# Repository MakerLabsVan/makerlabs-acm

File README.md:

# makerlabs-acm
MakerLabs Access Control Management (ACM) System

## How-to obtain this repo:
# Clone this repo recursively:
```
git clone --recursive https://github.com/MakerLabsVan/makerlabs-acm
cd makerlabs-acm
```

# Pre-requisites (macOS):

- Electrical:
  Install KiCad 5.0+:
  http://downloads.kicad-pcb.org/osx/nightly/

- Firmware/Software:
  Install homebrew macOS package manager:
  ```
  /usr/bin/ruby -e "$(curl -fsSL https://raw.githubusercontent.com/Homebrew/install/master/install)"
  ```

  Install `yarn`:
  ```
  brew install yarn
  ```

  Install dependencies:
  ```
  yarn deps
  yarn install
  ```

# Electrical

- Open the KiCad project:
  ```
  open -a kicad electrical/makerlabs-acm-reader-lock_v1.0.0.pro
  ```

# Firmware

- Configure firmware settings (Wifi SSID/password, Google Spreadsheet ID, etc):
  ```
  yarn firmware menuconfig
  ```

- Build a firmware image, flash it to the connected board:
  ```
  yarn firmware flash
  ```

- Same as above, but also monitor the serial data and reboot after flashing:
  ```
  yarn firmware flash monitor
  ```

- Build binaries for OTA firmware updates, upload them to Google Drive:
  (*note: increment the number in the `firmware/VERSION` file to allow clients to download it*)
  ```
  yarn firmware all_binaries && \
    gdrive update <firmware_image_id> firmware/build/makerlabs-acm-reader-lock.bin && \
    gdrive update <firmware_update_id> firmware/build/latest.fw.fb
  ```

# WebComponents

- Add WebComponent dependencies in webcomponents, via `bower`:
  ```
  yarn webcomponents-add <component names>
  ```

- Fetch/update WebComponent versions from latest packages:
  ```
  yarn webcomponents
  ```

Commit and push the updated files in `webcomponents/` and `webcomponents/bower_components/`

# Google Apps Script Webapp / Frontend

- Login to the Google Apps Script / online UI:
  ```
  yarn login
  ```

  Enable the Google Apps Script API for your personal Google Apps user:
  https://script.google.com/home/usersettings

- Pull changes from Google Apps Script / online UI:
  ```
  yarn pull
  ```

- (Make desired changes to files in `webapp/`)

- Push changes to Google Apps Script
  ```
  yarn push
  ```

- Deploy the latest changes as a webapp:
  ```
  yarn deploy
  ```

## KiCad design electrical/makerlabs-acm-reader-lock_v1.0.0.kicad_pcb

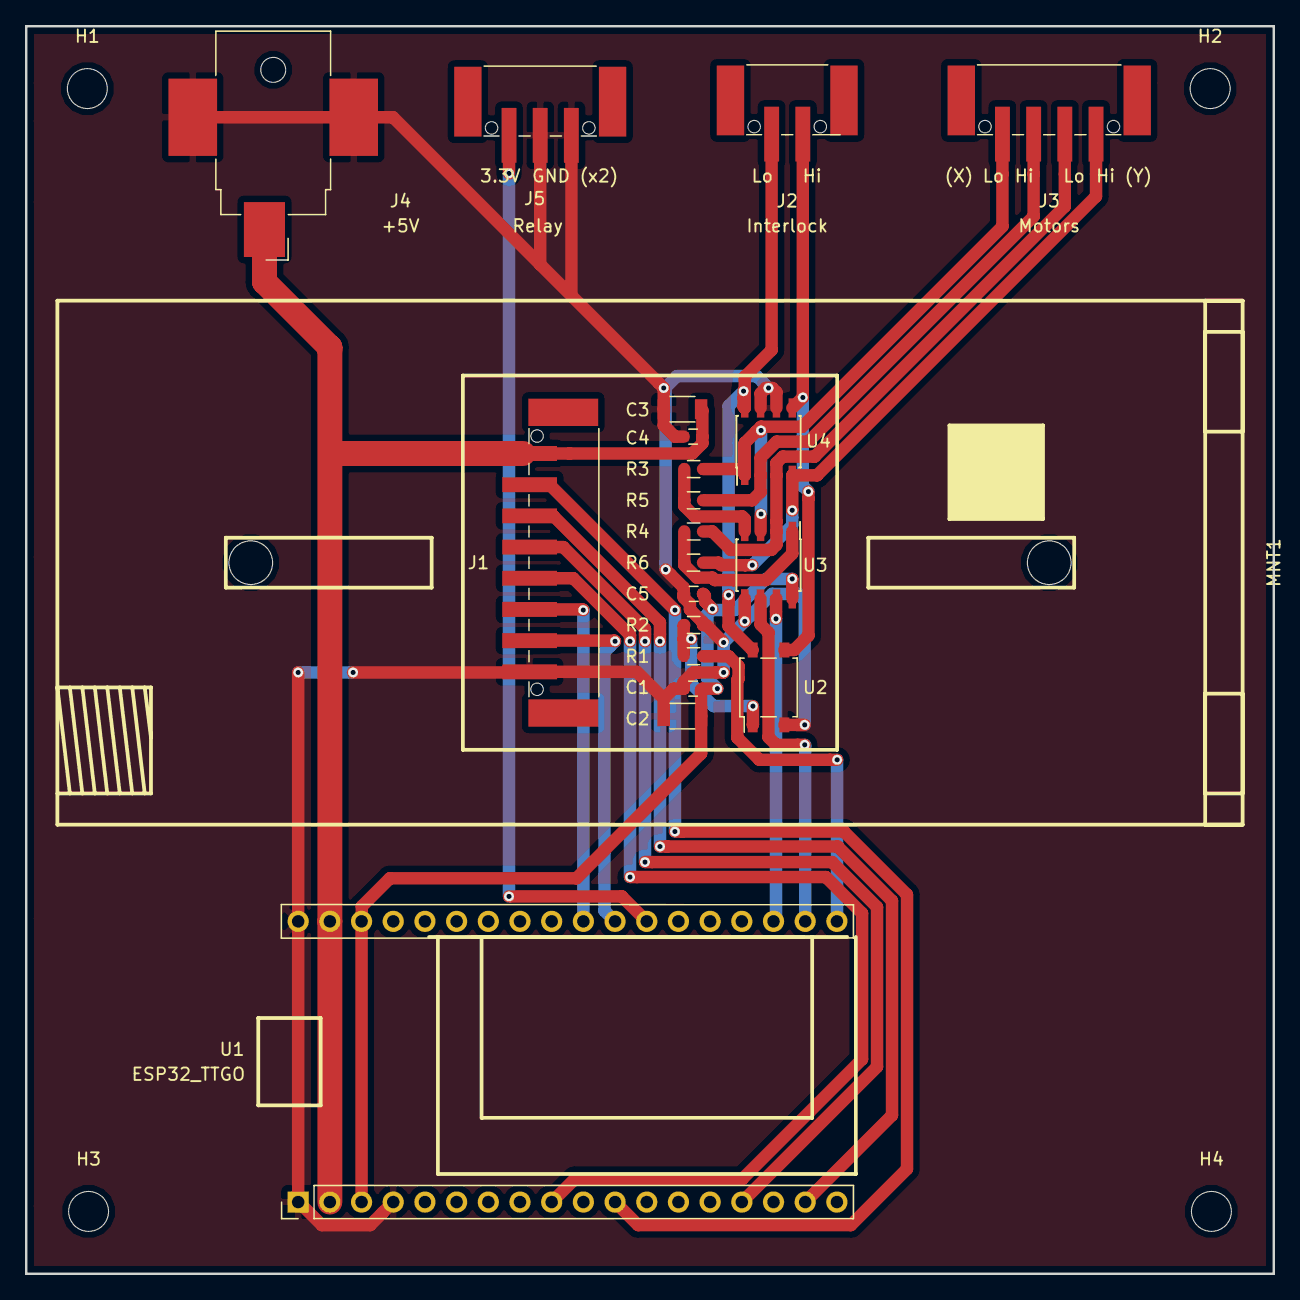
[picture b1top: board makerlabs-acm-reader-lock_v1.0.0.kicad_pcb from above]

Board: 2 copper layers, 100.0 x 100.0 mm, 25 parts (0 on the bottom side), 22 nets.

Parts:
C1, C4: 0.1uF; C_0603
C2, C3: 10uF; C_1206
C5: C; C_0603
H1, H2, H3, H4: Mounting_Hole; MountingHole_3.2mm_M3
J1: HID Reader; TerminalBlock_Phoenix_PTSM-0,5-8-HV-2.5-SMD_1x08_P2.50mm_Ve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
J2: Interlock; TerminalBlock_Phoenix_PTSM-0,5-2-HV-2.5-SMD_1x02_P2.50mm_Ve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
J3: Motors; TerminalBlock_Phoenix_PTSM-0,5-4-HV-2.5-SMD_1x06_P2.50mm_Ve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
J4: +5V; Barrel_Jack_CUI_PJ-036AH-SMT
J5: Relay; PhoenixContact_PTSM0,5_3-HV-2,5_SMD
MNT1: iClass_SE_R10_Backplate
R1: IR1; R_0603
R2: IR2; R_0603
R3: XR2; R_0603
R4: YR2; R_0603
R5: XR1; R_0603
R6: YR1; R_0603
U1: ESP32_TTGO
U2: ASSR-1218; SO-4_4.4x4.3mm_Pitch2.54mm
U3: TLP2161; SOIC-8_3.9x4.9mm_Pitch1.27mm
U4: SMDA15-6; SOIC-8_3.9x4.9mm_Pitch1.27mm

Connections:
+3V3: C1.1, C2.1, C5.2, U1.3, U1.34, U3.8
+5V: C3.1, C4.1, J1.1, J4.1, U1.2, U1.35
/Beeper: J1.2, U1.11
/DATA0: J1.6, U1.27
/DATA1: J1.7, U1.26
/Green_LED: J1.4, U1.15
/Interlock_H: J2.2, U2.3, U4.5
/Interlock_L: J2.1, U2.4, U4.8
/Interlock_Safe: R1.1, U1.19
/MotorX_H: J3.2, R5.1, U4.2
/MotorX_L: J3.1, R3.1, U3.3, U4.1
/MotorX_Safe: U1.20, U3.6
/MotorY_H: J3.4, R6.2, U4.4
/MotorY_L: J3.3, R4.2, U3.2, U4.3
/MotorY_Safe: U1.21, U3.7
/Read_Hold: J1.5, U1.9
/Red_LED: J1.3, U1.17
/Relay: J5.1, U1.25
GND: C1.2, C2.2, C3.2, C4.2, C5.1, J1.8, J4.2, J4.3, J5.2, J5.3, R2.2, U1.1, U1.4, U1.36, U2.2, U3.5, U4.6, U4.7
unnamed: R1.2, R2.1, U2.1
unnamed: R3.2, R5.2, U3.4
unnamed: R4.1, R6.1, U3.1

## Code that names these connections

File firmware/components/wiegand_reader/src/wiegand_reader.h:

#pragma once

#include <atomic>
#include <bitset>
#include <experimental/optional>

#include "timestamp.h"

#include "esp_attr.h"

using TagBits = std::bitset<26>;

struct TagRead
{
  uint64_t tag_id;
  TimeDuration timestamp;
};

class WiegandReader
{
public:
  struct Config
  {
    int data0_pin;
    int data1_pin;
    int hold_pin;
    int red_led_pin;
    int green_led_pin;
    int beeper_pin;
  };

  struct State
  {
    TagBits current_tag_bits;
    uint32_t current_bit = 0;
    TimeDuration last_bit_timestamp;
  };

  struct CallbackInfo
  {
    State& state;
    bool is_data1;
  };

  using TagReadEvent = std::experimental::optional<TagRead>;

  explicit WiegandReader(const Config& config = {});

  bool set_hold(bool enabled) IRAM_ATTR;
  bool set_red_led(bool enabled) IRAM_ATTR;
  bool set_green_led(bool enabled) IRAM_ATTR;
  bool set_beeper(bool enabled) IRAM_ATTR;

  TagReadEvent get_current_tag() IRAM_ATTR;

  //std::atomic<State> state;
  State state;

private:
  bool _set_output(int pin, bool enabled) IRAM_ATTR;
  Config config;

  // We give out the address to the global callback, though
  CallbackInfo data0_callback;
  CallbackInfo data1_callback;
};

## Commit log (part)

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2018-06-13 📦 Add generated es6-unbundled polymer build
2018-06-13 🐛 Remove leading / from base href in generated polymer build files
2018-06-26 💥 Change type of time field in Activity table to float64
2018-07-03 ⬆️ Upgrade firmware/esp-idf to latest master
2018-07-03 ♻️ Refactor firmware/main component to use a Google Cloud Function instead of talking to spreadsheets/gviz directly.
2018-07-03 ✨ Add webapp trigger to freeze the Makerlabs ID column of the Activity sheet (copying value out of formula into cell)
2018-07-03 🔊 Add debug logs to search webcomponent
2018-07-14 🔧 Remove blank lines from webcomponents/bower.json
2018-07-14 ➕ Add iron-jsonp-library dependency to webcomponents/bower.json
2018-07-14 🎨 Rename e parameter to req in webapp/views/*.js request handlers
2018-07-14 🐛 Remove check for 'INSERT_ROW' changeType in triggersForActivitySheet, allow it to run for timed events as well.
2018-07-14 📦 Regenerated webcomponents/build
2018-07-14 📦 Generated webcomponents/build
2018-07-14 📌 Update git SHA used in webcomponents/polymer.json
2018-07-14 📦 Regenerate webcomponents/build
2018-07-14 💥 Rename main webapp route to users-fields and ensure plural users is used consistently.
2018-07-16 ♻️ Convert functions/ from Google Cloud Functions (w/serverless) to Firebase Functions (w/firebase-tools)
2018-07-16 ✨ Add support for access_token passed as query string arg to google_apps_script_proxy function (to avoid CORS preflight checks for a GET request with no headers)
2018-07-16 ✨ Add support for ARRAYFORMULA/range values in webapp/macros/URLENCODE.js
2018-07-16 🔧 Use firebase function URL instead of cloud function in firmware/main component
2018-07-16 🔧 Add firebase.json config file with configuration for polymer webcomponents/ and dart functions/
2018-07-16 🔥 Remove unused top-level folder appsscript/
2018-07-16 🔧 Refactored top-level package.json into multiple sub package.json each with devDependencies and scripts necessary.
2018-07-16 📦 Updated webcomponents/build and webcomponents/bower_components
2018-07-17 🚨 Apply suggesting linting/formatting to all *.js files in webapp/
    via prettier
2018-07-17 🐛 Check for existence of choices array in each field, reverse the default order to [checked,unchecked]
2018-07-17 🐛 Update accessToken via populateAccessToken in app-shell component.
2018-07-17 🔖 Bump firmware/VERSION to 111
2018-07-20 📦 Update webcomponents/bower_components and webcomponents/build
2018-07-21 🚨 Fixup webcomponents/src/*.js with prettier
2018-07-21 👽 Convert webcomponents/view-user-page.html to Polymer 3
2018-07-21 👽 Update webcomponents/package.json to use Polymer 3 components, including local components in webcomponents/modulizer_workspace
2018-07-21 🐛 Set openid-prompt=select_account on google-signin component to allow user to select a new account for each login
2018-07-21 📦 Add webcomponents/yarn.lock file
2018-07-21 🚚 Rename top-level webapp/ folder to scripts/
2018-07-21 ♻️ Refactor webcomponents/src/user-search-bar to use LitElement
2018-07-21 ♻️ Refactor PolymerElement default value to LitElement in webcomponents/image-file-uploader.js
2018-08-03 ♻️ Refactor webcomponents/src/app-shell.js from PolymerElement to LitElement
2018-08-03 🐛 Add web-animations-js dependency, and add web-animations-next.min.js to polymer.json and as script in view-user-page.html
2018-08-03 ⬆️ Upgrade node_http package in functions/pubspec.yaml to 1.0.0-dev.7.0 which supports followRedirect behaviour by default.
2018-08-03 🔥 Remove unneeded _updateGridStyles from @polymer/app-layout grid, and use _firstRendered callback instead of connectedCallback to be sure DOM is finished.
2018-08-03 ✨ Add dynamic fetch/cache of Users columns datatable in functions/lib/permissions_check.dart
2018-08-03 ♻️ Replace hard-coded select/where columns with dynamic check in datatable in permissions_check
2018-08-03 🔧 Add serve and predeploy commands to webcomponents/package.json
2018-08-03 🎨 Remove trailing newlines in scripts/**/*.js
2018-08-03 🎨 Use 'yarn run push' instead of just 'yarn push'
2018-08-03 💥 Change epoch_seconds to epoch_milliseconds in generate_activity in firmware/main/acm_helpers.cpp
2018-08-03 💥 Add maker_status field to acm.fbs
    Add support for finding the current value from the User and storing it as part of Activity rows submitted to the spreadsheet in functions/lib/permissions_check
2018-08-03 🔥 Remove commented out code for separate actors in app_task
2018-08-03 ✨ Add support for separate template for alerts column
2018-08-03 ✨ Add helper function scripts/utils/getFirstEmptyRow.js
    To search through a Range and find the first entire row that is empty
2018-08-03 🐛 Parse response after creating a new User, and fill the row column so future updates will not create new users.
2018-08-03 ✨ Add support for automatically populating the MakerLabs ID field
2018-08-03 ✨ Add sendBrandedEmail template and function to Google Apps Scripts, using mui material components with HTML e-mail support.
2018-08-03 ✨ Add triggersForActivitySheet include trigger for sending usage emails, and billing emails.
2018-08-10 ➕ Add firebase dependency to webcomponents
2018-08-11 ⬆️ Upgrade functions firebase-* dependencies
2018-08-11 📦 Update functions/yarn.lock
2018-08-11 📄 Add missing CC-BY-NC-SA-4.0 license header
2018-08-11 ⬆️ Upgrade firebase-tools in webcomponents to 4.0.0
2018-08-11 ✨ Add Firebase RTDB to webcomponents
    To get pushed the latest_user activity as published by the permissions_check Firebase Function
2018-08-11 ✨ Play a beep sound when a user has alerts
2018-08-11 ✨ Add time-tracking, interlock, and relay support
2018-08-11 💥 Switch request.body flatbuffer type to string
2018-08-14 ⬆️ Upgrade flat_buffers to 1.9.2 in functions
2018-08-14 ➕ Add dependencies to functions for serverless-http
    To support running the same function handler on AWS Lambda as well as Google Cloud Functions / Firebase Functions.
2018-08-14 ⚡️ Add NODE_CLIENT global to permissions_check
    Initialize it with keepAlive: true and re-use wherever possible to avoid creating new connections to upstream services.
2018-08-14 🎨 Also allow configuring permissions_check from env vars
    Used in AWS Lambda
2018-08-14 🙈 Add .runtimeconfig.json to function/.gitignore
2018-08-14 ✨ Add functions/index-aws.js to use AWS Lambda
2018-08-26 ⬆️ Upgrade test dependency in functions/pubspec.yaml
2018-08-26 🔧 Remove webcomponents/firebase.js
    Use Firebase Hosting generated files in /__/firebase/ namespace
2018-08-26 🔧 Add project aliases to .firebaserc
2018-08-26 ⬆️ Upgrade firebase-tools to ^4.0.0
2018-08-26 🐛 Add firmware/main/assets/gen/.PLACEHOLDER
2018-08-26 🔒 Add storage.json for Firebase Storage rules
2018-09-14 📌 Pin wear_levelling dependency from esp-idf
    Use git commit 70e68c99d3b031dcd81c1f968387735332c9a453
2018-09-15 ✨ Add binary content types to serverless config
2018-09-15 🔊 Add log to ping early-exit in google_apps_script_proxy_http handler
2018-09-15 🔧 Update webcomponents/sw-precache-config.js
2018-09-21 🎨 Use an explicit case to double in generate_activity
2018-09-21 🎨 Add explicit verify for ACM::User in app_actor_behaviour
2018-09-21 🔧 Increase vfs_fat max_files to 10
2018-09-21 🚨 Add separate definition of app_main
2018-09-28 ⬆️ Upgrade esp32-network-lib submodule to latest master
2018-09-28 🔧 Update esp-idf make build files to match cmake
2018-09-28 📌 Pin esp32 component to last working version with patched mbedTLS
2018-09-28 🔥 Remove unused generated der cert for *.google.com
2018-10-03 🐛 Add column J (MakerLabs ID) to userSearchColumns in app-shell webcomponent
2018-10-03 🍱 Add webcomponents/images/defaultPhoto.png static image
2018-10-03 ⬆️ Upgrade all webcomponents dependencies to latest versions
2018-10-03 📦 Update with latest webcomponents/build
2018-10-03 🔧 Remove mqtt component from firmware/main/component.mk, it is not used
2018-10-03 🔧 Use 2.pool.ntp.org for NTP server, it provides IPv6 support
2018-10-03 🔥 Remove unused imports in view-user-form webcomponent
2018-10-13 🐛 Use MakerLabs GDrive profilePhotosFolderId in webcomponents/view-user-page.html
2018-12-06 💥 Move permissions_check function from Firebase functions to AWS Lambda/Serverless
2018-12-07 🔊 Add logs to permissions_check lambda handler
2019-01-21 🔧 Add '--fragment __/' to polymer serve for local firebase testing
2019-01-21 💄 Update branded email to include summary section, and change ordering
2019-01-21 ✨ Update email to use @makerlabs.com addresses
2019-01-21 🔧 Remove catch-all routing to /view-user-page.html
2019-01-21 📌 Pin firmware/components/esp32 to last-known good version
2019-01-21 🎨 Add BOM details to KiCad schematic
2019-01-21 ⬆️ Update KiCad mounting holes to KiCad 5 version
2019-01-21 🔧 Add electrical/bom.ini config file for KiBOM
2019-01-21 ✨ Add timeout_microseconds and retries to request_intent templates
2019-01-21 ✨ Add duration_microseconds field to ProgressBar table in display schema
2019-01-21 📦 Update generated acm_generated.h header file
2019-01-21 ♻️ Convert display actor to superloop
2019-01-21 ✨ Add y-axis support to machine_actor
2019-01-21 🐛 Enable RFID scanning at end of start_app, begin queuing events
2019-01-21 ♻️ Refactor app_actor to use updated display_actor and permissions_check_endpoint_actor
2019-02-09 📝 Add doxygen / API documentation for functions/
2019-02-09 🙈 Add firmware/fs/ directory to firmware/.gitignore
2019-02-09 💄 Add default generated doxygen layout configuration
    From running 'doxygen -l layoutfilename.xml'
2019-02-09 🙈 Remove *.css files from top-level .gitignore
2019-02-09 💄 Set max-width: 1100px on all doxygen images in HTML
2019-02-09 📝 Add Doxyfile
2019-02-09 📦 Add generated doxygen HTML in docs/
2019-02-09 📦 Regenerate doxygen HTML in docs/
2019-02-10 ⬆️ Upgrade lit-element, lit-html to stable versions (2.x, 1.x)
    Replace import ... from @polymer/lit-element with import ... from lit-element
2019-02-10 🎨 Update image-file-uploader to be parseable by doxygen
2019-02-10 🔧 Update postinstall script to install all modules recursively
2019-02-10 ➖ Remove unused top-level dependencies (some are already used by specific modules)
2019-02-12 ⬆️ Upgrade mbedtls component to include AES XTS support
2019-02-15 ⬆️ Upgrade lit-html and lit-element to stable versions
2019-02-16 🔧 Rename dev environment to test
2019-02-16 🎨 Move profilePhotosFolderId prop with other config props
2019-02-16 🔧 Add *.test and *.production scripts to webcomponents
2019-02-16 🔧 Add functions/.gitattributes for git-crypt'ing config.*.yml files
2019-02-16 🔧 Add *.test and *.production scripts in functions/package.json
2019-02-16 ⬆️ Upgrade firmware/components/mbedtls to latest master
2019-02-16 🔧 Use run_firmware_for_machine.sh script for 'yarn firmware'
2019-02-16 🚚 Move functions/.gitattributes to top-level .gitattributes
2019-02-16 🙈 Removed sdkconfig files from firmware/.gitignore
2019-02-16 🔧 Add build step as first step in no args firmware script
2019-02-16 📦 Add scripts/yarn.lock
2019-02-16 🔧 Remove top-level module scripts from package.json, replace with build.test/deploy.test, build.production/deploy.production
2019-02-16 ➕ Add top-level dependency yarn-run-all
2019-02-16 🔧 Add deploy.*:firebase and deploy.*:aws scripts to functions
2019-02-17 🔧 Use 'command -v' in package.json scripts and check for commands before attempting 'brew install'
2019-02-17 ➕ Add dev dependency replace-in-file to scripts/package.json
2019-02-17 ➕ Add dev dependencies for NodeJS Google OAuth
2019-02-17 🔧 Use 'yarn run' for custom scripts
2019-02-17 🔧 Add login:* custom scripts
2019-02-17 🔧 Remove caddy from deps and add aws/awscli
2019-02-17 🔧 Add 'brew tap dart-lang/dart' and 'brew install dart' to 'yarn deps'
2019-02-17 🔧 Remove awscli from 'yarn deps', use 'sls config credentials' in functions 'login:aws'
2019-02-24 📝 Add module-level docs and KNOWN_ISSUES
